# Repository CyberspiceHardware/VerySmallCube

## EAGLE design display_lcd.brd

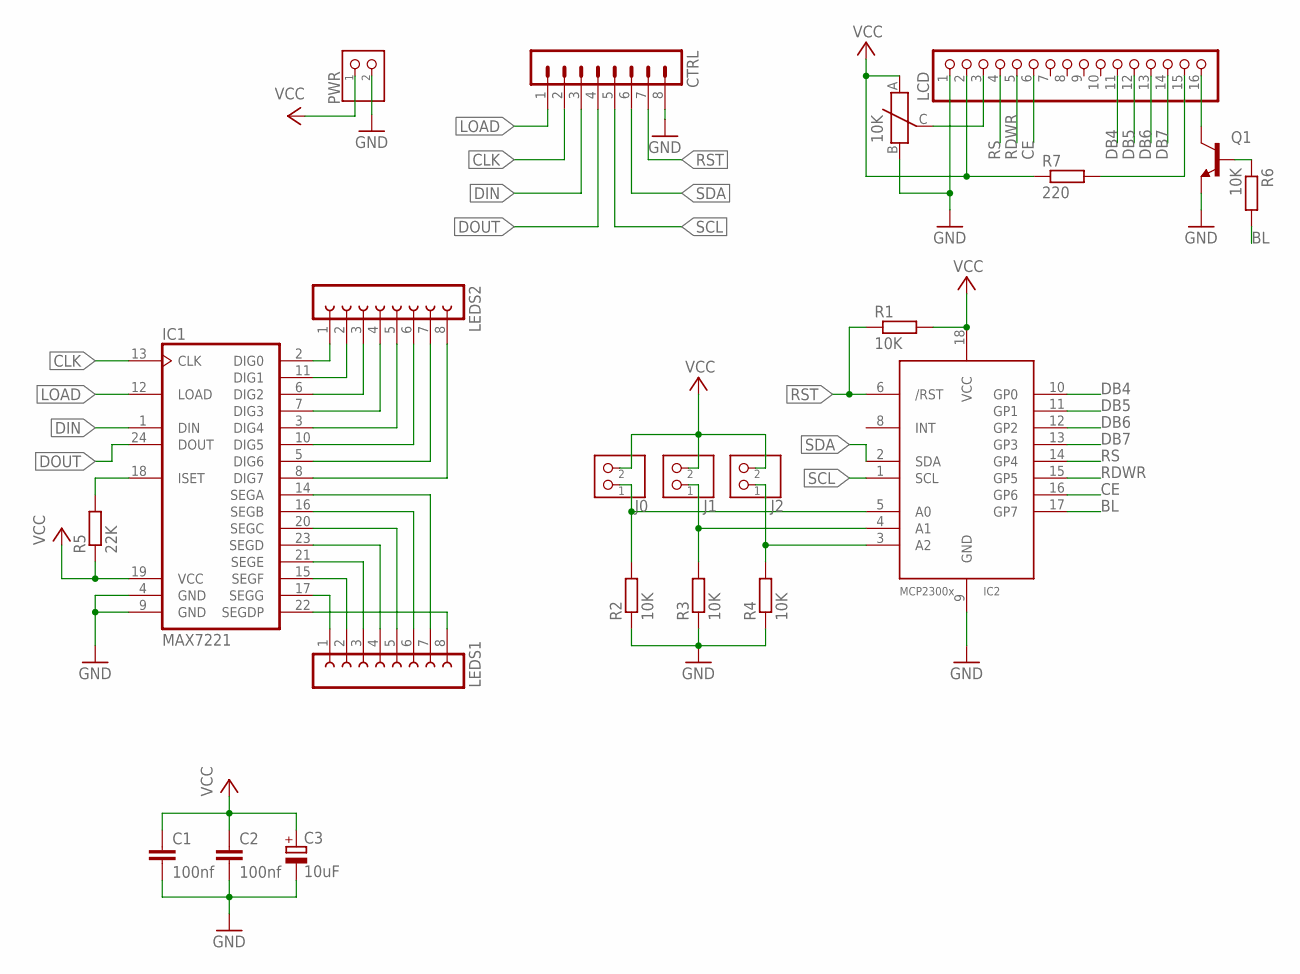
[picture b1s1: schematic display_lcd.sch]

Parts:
C1, C2: 100nf; C025-024X044
C3: 10uF; E2,5-6E
CTRL: MA08-1
IC1: MAX7221; DIL24-3
IC2: MCP2300X/P; DIL18
J0, J1, J2: PINS-1X2; 1X2
LCD: PINS-1X16; 1X16
LEDS1, LEDS2: FE08-1; FE08
PWR: PINS-1X2; 1X2
Q1: BC547; TO92
R1, R2, R3, R4, R6: 10K; 0204/7
R5: 22K; 0204/7
R7: 220; 0204/7
U$1: 10K; TRIM3MM

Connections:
BL: IC2.17 (GP7), R6.2
CE: IC2.16 (GP6), LCD.6
CLK: CTRL.2, IC1.13 (CLK)
DB4: IC2.10 (GP0), LCD.11
DB5: IC2.11 (GP1), LCD.12
DB6: IC2.12 (GP2), LCD.13
DB7: IC2.13 (GP3), LCD.14
DIN: CTRL.3, IC1.1 (DIN)
DOUT: CTRL.4, IC1.24 (DOUT)
GND: C1.2, C2.2, C3.-, CTRL.8, IC1.4 (GND), IC1.9 (GND), IC2.9 (GND), LCD.1, PWR.P2 (2), Q1.1 (E), R2.1, R3.1, R4.1, U$1.B
LOAD: CTRL.1, IC1.12 (LOAD)
unnamed: IC1.2 (DIG0), LEDS2.1
unnamed: IC1.11 (DIG1), LEDS2.2
unnamed: IC1.6 (DIG2), LEDS2.3
unnamed: IC1.7 (DIG3), LEDS2.4
unnamed: IC1.3 (DIG4), LEDS2.5
unnamed: IC1.10 (DIG5), LEDS2.6
unnamed: IC1.5 (DIG6), LEDS2.7
unnamed: IC1.8 (DIG7), LEDS2.8
unnamed: IC1.17 (SEGG), LEDS1.1
unnamed: IC1.15 (SEGF), LEDS1.2
unnamed: IC1.21 (SEGE), LEDS1.3
unnamed: IC1.23 (SEGD), LEDS1.4
unnamed: IC1.20 (SEGC), LEDS1.5
unnamed: IC1.16 (SEGB), LEDS1.6
unnamed: IC1.14 (SEGA), LEDS1.7
unnamed: IC1.22 (SEGDP), LEDS1.8
unnamed: IC1.18 (ISET), R5.2
unnamed: IC2.4 (A1), J1.P1 (1), R3.2
unnamed: IC2.3 (A2), J2.P1 (1), R4.2
unnamed: LCD.3, U$1.C
unnamed: IC2.5 (A0), J0.P1 (1), R2.2
unnamed: LCD.16, Q1.3 (C)
unnamed: Q1.2 (B), R6.1
unnamed: LCD.15, R7.2
RDWR: IC2.15 (GP5), LCD.5
RS: IC2.14 (GP4), LCD.4
RST: CTRL.7, IC2.6 (/RST), R1.1
SCL: CTRL.5, IC2.1 (SCL)
SDA: CTRL.6, IC2.2 (SDA)
VCC: C1.1, C2.1, C3.+, IC1.19 (VCC), IC2.18 (VCC), J0.P2 (2), J1.P2 (2), J2.P2 (2), LCD.2, PWR.P1 (1), R1.2, R5.1, R7.1, U$1.A

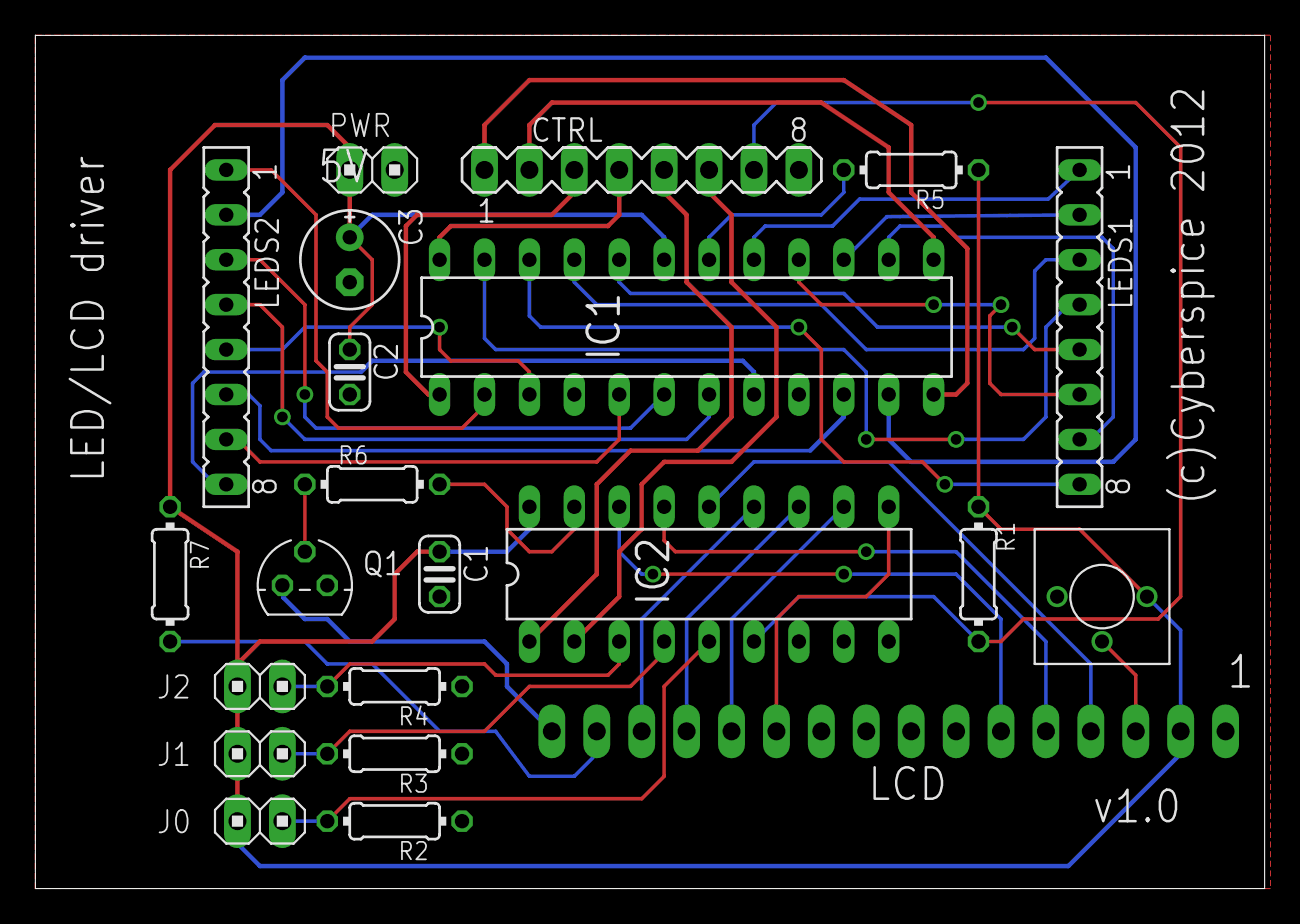
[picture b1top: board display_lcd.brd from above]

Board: 2 copper layers, 69.5 x 48.2 mm, 22 parts (1 on the bottom side), 41 nets.

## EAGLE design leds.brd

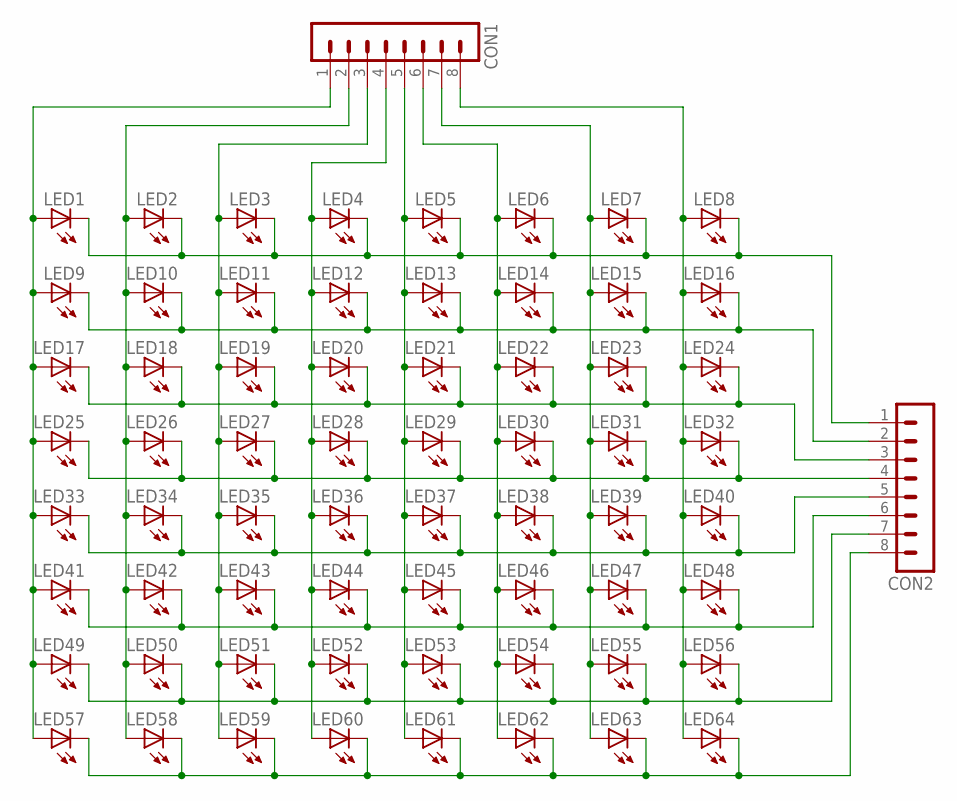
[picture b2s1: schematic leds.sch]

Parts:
CON1, CON2: MA08-1
LED1, LED2, LED3, LED4, LED5, LED6, LED7, LED8, LED9, LED10, LED11, LED12, LED13, LED14, LED15, LED16, LED17, LED18, LED19, LED20, LED21, LED22, LED23, LED24, LED25, LED26, LED27, LED28, LED29, LED30, LED31, LED32, LED33, LED34, LED35, LED36, LED37, LED38, LED39, LED40, LED41, LED42, LED43, LED44, LED45, LED46, LED47, LED48, LED49, LED50, LED51, LED52, LED53, LED54, LED55, LED56, LED57, LED58, LED59, LED60, LED61, LED62, LED63, LED64: LED3MM

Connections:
unnamed: CON1.1, LED1.A, LED9.A, LED17.A, LED25.A, LED33.A, LED41.A, LED49.A, LED57.A
unnamed: CON1.2, LED2.A, LED10.A, LED18.A, LED26.A, LED34.A, LED42.A, LED50.A, LED58.A
unnamed: CON1.3, LED3.A, LED11.A, LED19.A, LED27.A, LED35.A, LED43.A, LED51.A, LED59.A
unnamed: CON1.4, LED4.A, LED12.A, LED20.A, LED28.A, LED36.A, LED44.A, LED52.A, LED60.A
unnamed: CON1.5, LED5.A, LED13.A, LED21.A, LED29.A, LED37.A, LED45.A, LED53.A, LED61.A
unnamed: CON1.6, LED6.A, LED14.A, LED22.A, LED30.A, LED38.A, LED46.A, LED54.A, LED62.A
unnamed: CON1.7, LED7.A, LED15.A, LED23.A, LED31.A, LED39.A, LED47.A, LED55.A, LED63.A
unnamed: CON1.8, LED8.A, LED16.A, LED24.A, LED32.A, LED40.A, LED48.A, LED56.A, LED64.A
unnamed: CON2.8, LED57.K (C), LED58.K (C), LED59.K (C), LED60.K (C), LED61.K (C), LED62.K (C), LED63.K (C), LED64.K (C)
unnamed: CON2.7, LED49.K (C), LED50.K (C), LED51.K (C), LED52.K (C), LED53.K (C), LED54.K (C), LED55.K (C), LED56.K (C)
unnamed: CON2.6, LED41.K (C), LED42.K (C), LED43.K (C), LED44.K (C), LED45.K (C), LED46.K (C), LED47.K (C), LED48.K (C)
unnamed: CON2.5, LED33.K (C), LED34.K (C), LED35.K (C), LED36.K (C), LED37.K (C), LED38.K (C), LED39.K (C), LED40.K (C)
unnamed: CON2.4, LED25.K (C), LED26.K (C), LED27.K (C), LED28.K (C), LED29.K (C), LED30.K (C), LED31.K (C), LED32.K (C)
unnamed: CON2.3, LED17.K (C), LED18.K (C), LED19.K (C), LED20.K (C), LED21.K (C), LED22.K (C), LED23.K (C), LED24.K (C)
unnamed: CON2.2, LED9.K (C), LED10.K (C), LED11.K (C), LED12.K (C), LED13.K (C), LED14.K (C), LED15.K (C), LED16.K (C)
unnamed: CON2.1, LED1.K (C), LED2.K (C), LED3.K (C), LED4.K (C), LED5.K (C), LED6.K (C), LED7.K (C), LED8.K (C)

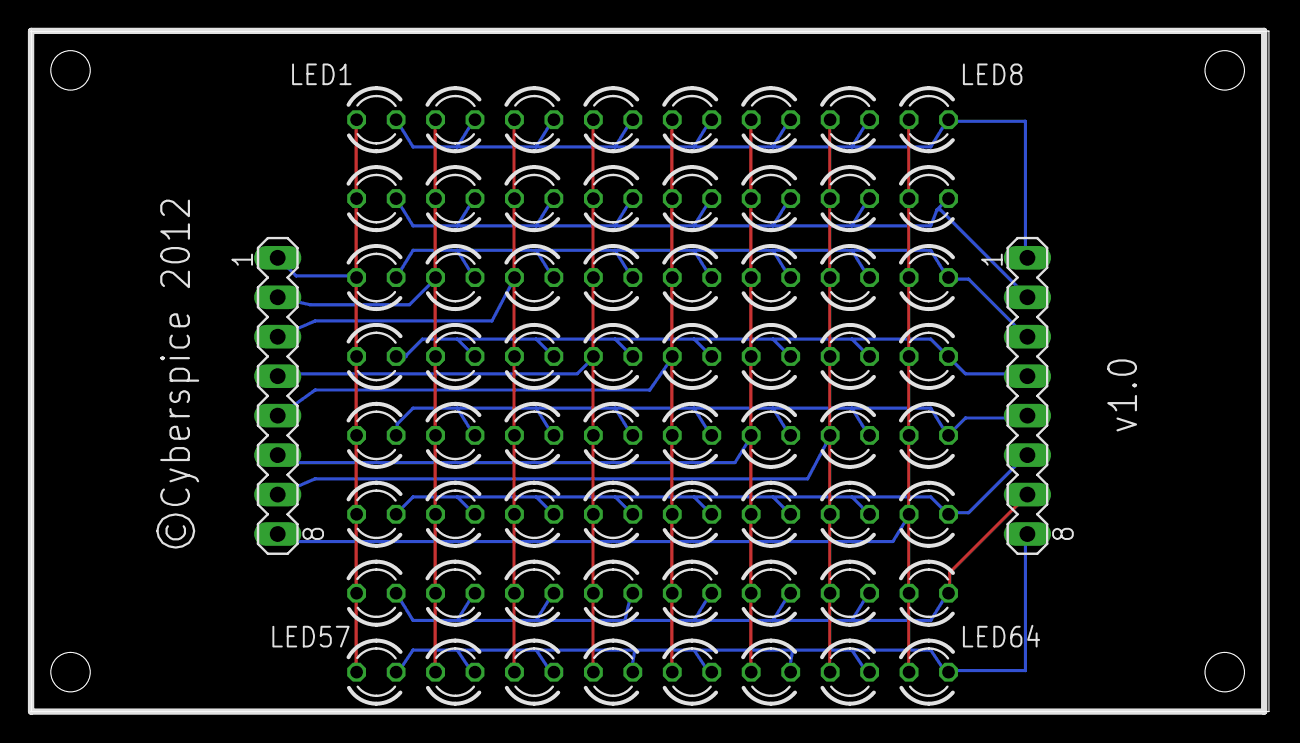
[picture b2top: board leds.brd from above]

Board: 2 copper layers, 79.7 x 43.8 mm, 66 parts (0 on the bottom side), 16 nets.

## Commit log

2012-11-11 Initial commit of the VerySmallCube schematics and board files.
    Files added:
    display.brd
    display.sch
    leds.brd
    leds.sch
2012-11-11 Added RD/WR line as bit 5. This moved CE to bit 6 and Backlight to bit 7. Allows reading of LCD status. Also needed to support OLED displays.
    Files modified:
    display.brd
    display.sch
2012-11-11 Fixed ERC issue to do with mis-aligned track.
    Files modified:
    display.brd
2013-01-14 Moved display.brd and display.sch to display_lcd.brd and display_lcd.sch.
    Updated display.brd and display.sch to support OLED. I.e. removed
    unnecessary components.
2013-04-08 Adding CAD files for laser cutting the perspex cube.
    Files added:
    cube1.dxf
    cube2.dxf
    cube3.dxf
2013-04-08 Added labels and back holes.
    Files modified:
    cube1.dxf
    cube2.dxf
    cube3.dxf
2013-04-09 Resized each face of the cube to be 130mm square. Added holes for beaglebone sockets.
    Files modified:
    cube1.dxf
    cube2.dxf
    cube3.dxf
2013-04-10 Adjusted the back panel cutouts for the beaglebone. It didn't quite fit before.
    Files modified:
    cube3.dxf

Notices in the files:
leds.brd:
©Cyberspice 2012
